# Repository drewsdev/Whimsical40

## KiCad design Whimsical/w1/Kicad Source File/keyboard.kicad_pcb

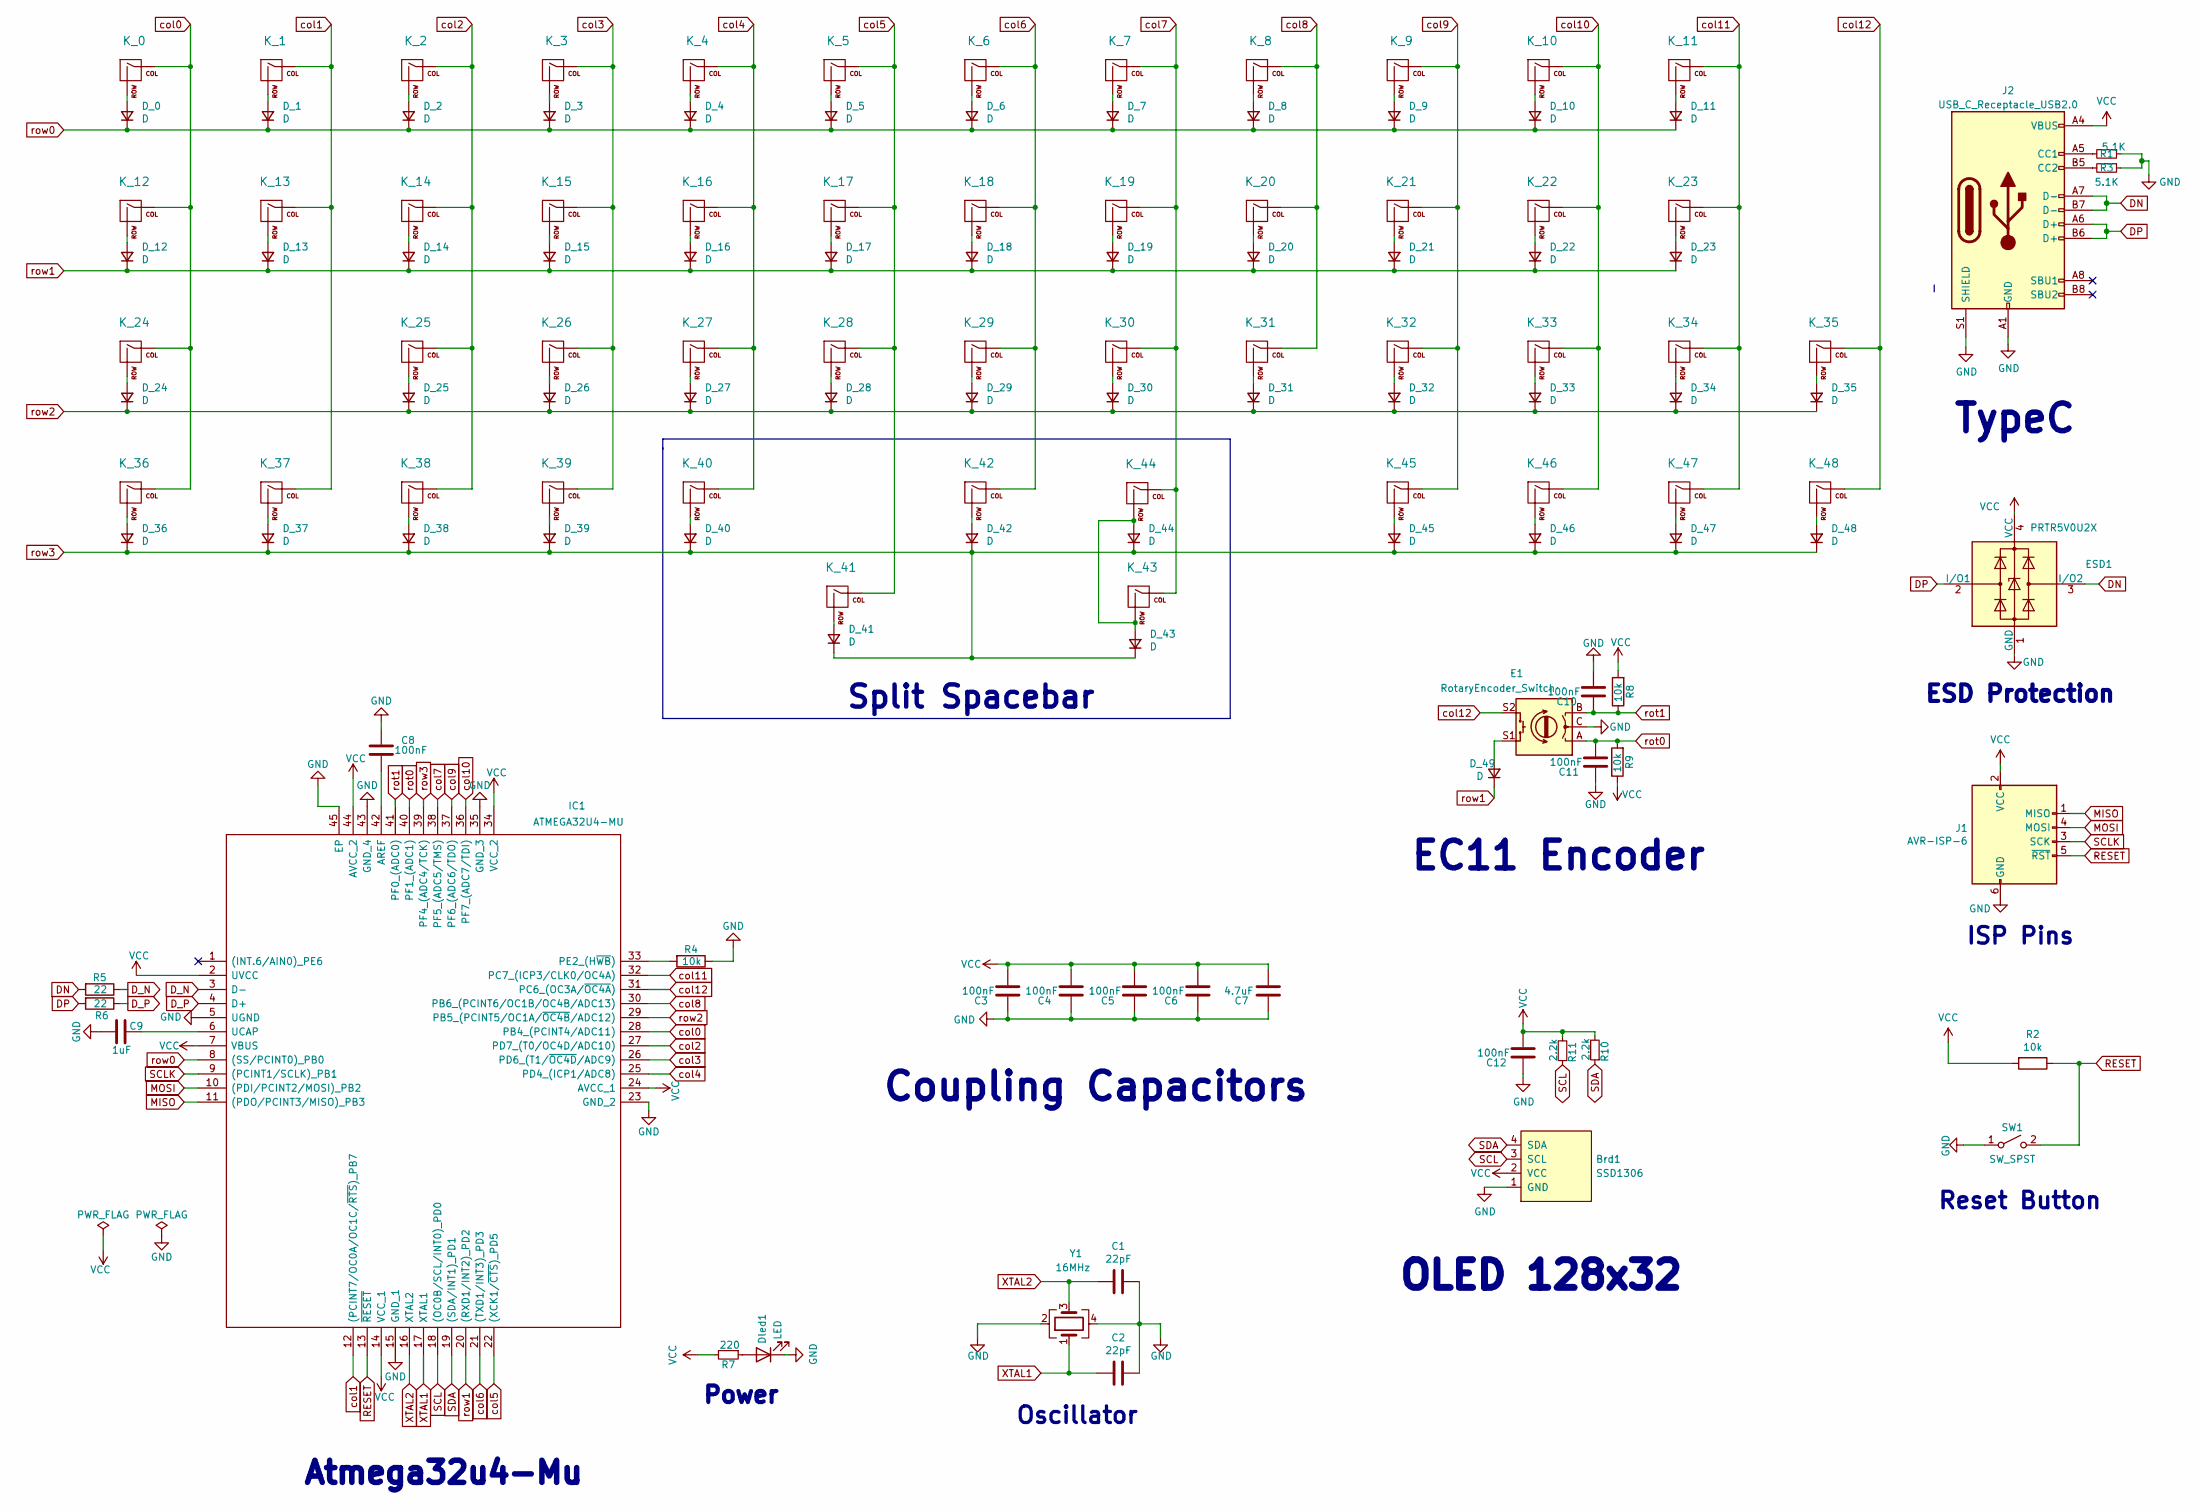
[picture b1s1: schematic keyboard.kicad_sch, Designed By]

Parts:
Brd1: SSD1306; 128x64OLED_128x64
C1, C2: 22pF; C_0603_1608Metric
C3, C4, C5, C6, C8, C10, C11, C12: 100nF; C_0603_1608Metric
C7: 4.7uF; C_0603_1608Metric
C9: 1uF; C_0603_1608Metric
D_0, D_1, D_2, D_3, D_4, D_5, D_6, D_7, D_8, D_9, D_10, D_11, D_12, D_13, D_14, D_15, D_16, D_17, D_18, D_19, D_20, D_21, D_22, D_23, D_24, D_25, D_26, D_27, D_28, D_29, D_30, D_31, D_32, D_33, D_34, D_35, D_36, D_37, D_38, D_39, D_40, D_41, D_42, D_43, D_44, D_45, D_46, D_47, D_48, D_49: D; D_SOD-123
Dled1: LED; LED_0603_1608Metric; LCSC C473820
E1: RotaryEncoder_Switch; RotaryEncoder_Alps_EC11E-Switch_Vertical_H20mm
ESD1: PRTR5V0U2X; LCSC C2827688
IC1: ATMEGA32U4-MU; QFN50P700X700X100-45N-D; Manufacturer_Part_Number ATMEGA32U4-MU; Mouser Part Number 556-ATMEGA32U4-MU
J1: AVR-ISP-6; ISP
J2: USB_C_Receptacle_USB2.0; USB_C_Receptacle_HRO_TYPE-C-31-M-12
K_0, K_1, K_2, K_3, K_4, K_5, K_6, K_7, K_8, K_9, K_10, K_13, K_14, K_15, K_16, K_17, K_18, K_19, K_20, K_21, K_22, K_25, K_26, K_27, K_28, K_29, K_30, K_31, K_32, K_33, K_34, K_35, K_36, K_37, K_38, K_39, K_45, K_46, K_47, K_48: KEYSW; MXOnly-1U-Hotswap-Solder
K_11, K_24: KEYSW; MX-1.5U-NoLED-solder
K_12, K_23, K_40, K_44: KEYSW; CherryMX_1.250u_PCB_KailhSocket-solder
K_41, K_43: KEYSW; MX-2.25U-ReversedStabilizers-NoLED-flip
K_42: KEYSW; Reverse-MXOnly-2U-Hotswap+normal
R1, R3: 5.1K; R_0603_1608Metric
R2: 10k; R_0603_1608Metric; LCSC Part # C17414
R4, R8, R9: 10k; R_0603_1608Metric
R5, R6: 22; R_0603_1608Metric
R7: 220; R_0603_1608Metric
R10, R11: 2.2k; R_0603_1608Metric
SW1: SW_SPST; K2-1187SQ-A4SW-06; Manufacturer Part Number K2-1187SQ-A4SW-06
Y1: 16MHz; Crystal_SMD_3225-4Pin_3.2x2.5mm; LCSC Part # C13738

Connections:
DN: ESD1.3 (I/O2), J2.A7 (D-), J2.B7 (D-), R5.2
DP: ESD1.2 (I/O1), J2.A6 (D+), J2.B6 (D+), R6.2
D_N: IC1.3 (D-), R5.1
D_P: IC1.4 (D+), R6.1
GND: Brd1.1 (GND), C1.1, C2.1, C3.2, C4.2, C5.2, C6.2, C7.2, C8.2, C9.2, C10.1, C11.2, C12.2, Dled1.1 (K), E1.C, ESD1.1 (GND), IC1.5 (UGND), IC1.15 (GND_1), IC1.23 (GND_2), IC1.35 (GND_3), IC1.43 (GND_4), IC1.45 (EP), J1.6 (GND), J2.A1 (GND), J2.A12 (GND), J2.B1 (GND), J2.B12 (GND), J2.S1 (SHIELD), R1.1, R3.1, R4.1, SW1.1 (A), Y1.2, Y1.4
MISO: IC1.11 ((PDO/PCINT3/MISO)_PB3), J1.1 (MISO)
MOSI: IC1.10 ((PDI/PCINT2/MOSI)_PB2), J1.4 (MOSI)
unnamed: C8.1, IC1.42 (AREF)
unnamed: C9.1, IC1.6 (UCAP)
unnamed: D_0.2 (A), K_0.2 (ROW)
unnamed: D_1.2 (A), K_1.2 (ROW)
unnamed: D_2.2 (A), K_2.2 (ROW)
unnamed: D_3.2 (A), K_3.2 (ROW)
unnamed: D_4.2 (A), K_4.2 (ROW)
unnamed: D_5.2 (A), K_5.2 (ROW)
unnamed: D_6.2 (A), K_6.2 (ROW)
unnamed: D_7.2 (A), K_7.2 (ROW)
unnamed: D_8.2 (A), K_8.2 (ROW)
unnamed: D_9.2 (A), K_9.2 (ROW)
unnamed: D_10.2 (A), K_10.2 (ROW)
unnamed: D_11.2 (A), K_11.2 (ROW)
unnamed: D_12.2 (A), K_12.2 (ROW)
unnamed: D_13.2 (A), K_13.2 (ROW)
unnamed: D_14.2 (A), K_14.2 (ROW)
unnamed: D_15.2 (A), K_15.2 (ROW)
unnamed: D_16.2 (A), K_16.2 (ROW)
unnamed: D_17.2 (A), K_17.2 (ROW)
unnamed: D_18.2 (A), K_18.2 (ROW)
unnamed: D_19.2 (A), K_19.2 (ROW)
unnamed: D_20.2 (A), K_20.2 (ROW)
unnamed: D_21.2 (A), K_21.2 (ROW)
unnamed: D_22.2 (A), K_22.2 (ROW)
unnamed: D_23.2 (A), K_23.2 (ROW)
unnamed: D_24.2 (A), K_24.2 (ROW)
unnamed: D_25.2 (A), K_25.2 (ROW)
unnamed: D_26.2 (A), K_26.2 (ROW)
unnamed: D_27.2 (A), K_27.2 (ROW)
unnamed: D_28.2 (A), K_28.2 (ROW)
unnamed: D_29.2 (A), K_29.2 (ROW)
unnamed: D_30.2 (A), K_30.2 (ROW)
unnamed: D_31.2 (A), K_31.2 (ROW)
unnamed: D_32.2 (A), K_32.2 (ROW)
unnamed: D_33.2 (A), K_33.2 (ROW)
unnamed: D_34.2 (A), K_34.2 (ROW)
unnamed: D_35.2 (A), K_35.2 (ROW)
unnamed: D_36.2 (A), K_36.2 (ROW)
unnamed: D_37.2 (A), K_37.2 (ROW)
unnamed: D_38.2 (A), K_38.2 (ROW)
unnamed: D_39.2 (A), K_39.2 (ROW)
unnamed: D_40.2 (A), K_40.2 (ROW)
unnamed: D_41.2 (A), K_41.2 (ROW)
unnamed: D_42.2 (A), K_42.2 (ROW)
unnamed: D_43.2 (A), D_44.2 (A), K_43.2 (ROW), K_44.2 (ROW)
unnamed: D_45.2 (A), K_45.2 (ROW)
unnamed: D_46.2 (A), K_46.2 (ROW)
unnamed: D_47.2 (A), K_47.2 (ROW)
unnamed: D_48.2 (A), K_48.2 (ROW)
unnamed: Dled1.2 (A), R7.1
unnamed: D_49.2 (A), E1.S1
unnamed: IC1.33 (PE2_(H~WB)), R4.2
unnamed: J2.A5 (CC1), R1.2
unnamed: J2.B5 (CC2), R3.2
RESET: IC1.13 (~RESET), J1.5 (~RST), R2.1, SW1.2 (B)
SCL: Brd1.3 (SCL), IC1.18 ((OC0B/SCL/INT0)_PD0), R11.1
SCLK: IC1.9 ((PCINT1/SCLK)_PB1), J1.3 (SCK)
SDA: Brd1.4 (SDA), IC1.19 ((SDA/INT1)_PD1), R10.1
VCC: Brd1.2 (VCC), C3.1, C4.1, C5.1, C6.1, C7.1, C12.1, ESD1.4 (VCC), IC1.2 (UVCC), IC1.7 (VBUS), IC1.14 (VCC_1), IC1.24 (AVCC_1), IC1.34 (VCC_2), IC1.44 (AVCC_2), J1.2 (VCC), J2.A4 (VBUS), J2.A9 (VBUS), J2.B4 (VBUS), J2.B9 (VBUS), R2.2, R7.2, R8.2, R9.1, R10.2, R11.2
XTAL1: C2.2, IC1.17 (XTAL1), Y1.1
XTAL2: C1.2, IC1.16 (XTAL2), Y1.3
col0: IC1.28 (PB4_(PCINT4/ADC11)), K_0.1 (COL), K_12.1 (COL), K_24.1 (COL), K_36.1 (COL)
col1: IC1.12 ((PCINT7/OC0A/OC1C/~RTS)_PB7), K_1.1 (COL), K_13.1 (COL), K_37.1 (COL)
col2: IC1.27 (PD7_(T0/OC4D/ADC10)), K_2.1 (COL), K_14.1 (COL), K_25.1 (COL), K_38.1 (COL)
col3: IC1.26 (PD6_(T1/~OC4D/ADC9)), K_3.1 (COL), K_15.1 (COL), K_26.1 (COL), K_39.1 (COL)
col4: IC1.25 (PD4_(ICP1/ADC8)), K_4.1 (COL), K_16.1 (COL), K_27.1 (COL), K_40.1 (COL)
col5: IC1.22 ((XCK1/~CTS)_PD5), K_5.1 (COL), K_17.1 (COL), K_28.1 (COL), K_41.1 (COL)
col6: IC1.21 ((TXD1/INT3)_PD3), K_6.1 (COL), K_18.1 (COL), K_29.1 (COL), K_42.1 (COL)
col7: IC1.38 (PF5_(ADC5/TMS)), K_7.1 (COL), K_19.1 (COL), K_30.1 (COL), K_43.1 (COL), K_44.1 (COL)
col8: IC1.30 (PB6_(PCINT6/OC1B/OC4B/ADC13)), K_8.1 (COL), K_20.1 (COL), K_31.1 (COL)
col9: IC1.37 (PF6_(ADC6/TDO)), K_9.1 (COL), K_21.1 (COL), K_32.1 (COL), K_45.1 (COL)
col10: IC1.36 (PF7_(ADC7/TDI)), K_10.1 (COL), K_22.1 (COL), K_33.1 (COL), K_46.1 (COL)
col11: IC1.32 (PC7_(ICP3/CLK0/OC4A)), K_11.1 (COL), K_23.1 (COL), K_34.1 (COL), K_47.1 (COL)
col12: E1.S2, IC1.31 (PC6_(OC3A/~OC4A)), K_35.1 (COL), K_48.1 (COL)
rot0: C11.1, E1.A, IC1.40 (PF1_(ADC1)), R9.2
rot1: C10.2, E1.B, IC1.41 (PF0_(ADC0)), R8.1
row0: D_0.1 (K), D_1.1 (K), D_2.1 (K), D_3.1 (K), D_4.1 (K), D_5.1 (K), D_6.1 (K), D_7.1 (K), D_8.1 (K), D_9.1 (K), D_10.1 (K), D_11.1 (K), IC1.8 ((SS/PCINT0)_PB0)
row1: D_12.1 (K), D_13.1 (K), D_14.1 (K), D_15.1 (K), D_16.1 (K), D_17.1 (K), D_18.1 (K), D_19.1 (K), D_20.1 (K), D_21.1 (K), D_22.1 (K), D_23.1 (K), D_49.1 (K), IC1.20 ((RXD1/INT2)_PD2)
row2: D_24.1 (K), D_25.1 (K), D_26.1 (K), D_27.1 (K), D_28.1 (K), D_29.1 (K), D_30.1 (K), D_31.1 (K), D_32.1 (K), D_33.1 (K), D_34.1 (K), D_35.1 (K), IC1.29 (PB5_(PCINT5/OC1A/~OC4B/ADC12))
row3: D_36.1 (K), D_37.1 (K), D_38.1 (K), D_39.1 (K), D_40.1 (K), D_41.1 (K), D_42.1 (K), D_43.1 (K), D_44.1 (K), D_45.1 (K), D_46.1 (K), D_47.1 (K), D_48.1 (K), IC1.39 (PF4_(ADC4/TCK))

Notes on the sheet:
Coupling Capacitors
Atmega32u4-Mu
ISP Pins
Reset Button
Power
ESD Protection
OLED 128x32
Oscillator
EC11 Encoder
TypeC
Split Spacebar

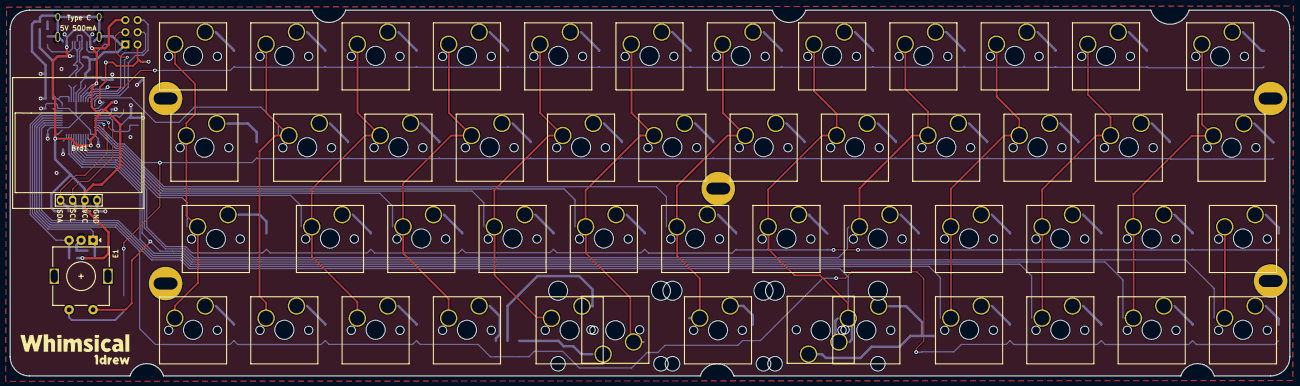
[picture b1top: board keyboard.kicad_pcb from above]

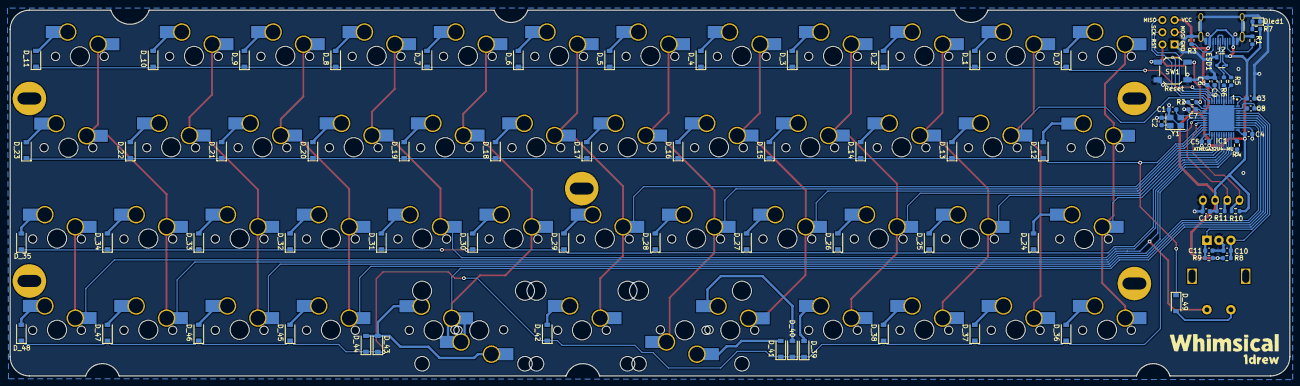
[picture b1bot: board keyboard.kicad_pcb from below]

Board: 2 copper layers, 267.0 x 76.3 mm, 131 parts (129 on the bottom side), 88 nets.

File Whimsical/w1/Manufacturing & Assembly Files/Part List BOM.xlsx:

Item | Qty | Reference(s) | Value | LibPart | Footprint | JLCPCB Part#
1 | 1 | Brd1 | SSD1306 | SSD1306-128x64_OLED:SSD1306 | SSD1306 OLED:128x64OLED_128x64 | https://www.aliexpress.com/i/32780054633.html
2 | 2 | C1, C2 | 22pF | Device:C | CherryMX_KailhSocket:C_0603_1608Metric | C1653
3 | 8 | C3, C4, C5, C6, C8, C10, C11, C12 | 100nF | Device:C | CherryMX_KailhSocket:C_0603_1608Metric | C14663
4 | 1 | C7 | 4.7uF | Device:C | CherryMX_KailhSocket:C_0603_1608Metric | C19666
5 | 1 | C9 | 1uF | Device:C | CherryMX_KailhSocket:C_0603_1608Metric | C15849
6 | 50 | D_0, D_1, D_2, D_3, D_4, D_5, D_6, D_7, D_8, D_9, D_10, D_11, D_12, D_13, D_14,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 | D | Device:D_Small | Diode_SMD:D_SOD-123 | C81598
7 | 1 | Dled1 | LED | Device:LED | LED_SMD:LED_0603_1608Metric | C72038
8 | 1 | E1 | RotaryEncoder_Switch | Device:RotaryEncoder_Switch | CherryMX_KailhSocket:RotaryEncoder_Alps_EC11E-Switch_Vertical_H20mm | C1322545
9 | 1 | ESD1 | PRTR5V0U2X | Power_Protection:PRTR5V0U2X | CherryMX_KailhSocket:PRTR5V0U2X | C2827688
10 | 1 | IC1 | ATMEGA32U4-MU | ATMEGA32U4-MU:ATMEGA32U4-MU | QFN50P700X700X100-45N-D | C112161
11 | 1 | J2 | USB_C_Receptacle_USB2.0 | :USB_C_Receptacle_USB2.0_1 | CherryMX_KailhSocket:USB_C_Receptacle_HRO_TYPE-C-31-M-12 | C165948
12 | 40 | K_0, K_1, K_2, K_3, K_4, K_5, K_6, K_7, K_8, K_9, K_10, K_13, K_14, K_15, K_16,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 | KEYSW | MX_Alps_Hybrid:MX-NoLED | CherryMX_KailhSocket:MXOnly-1U-Hotswap-Solder | C2803348
13 | 2 | K_11, K_24 | KEYSW | MX_Alps_Hybrid:MX-NoLED | CherryMX_KailhSocket:MX-1.5U-NoLED-solder | C2803348
14 | 4 | K_12, K_23, K_40, K_44 | KEYSW | MX_Alps_Hybrid:MX-NoLED | CherryMX_KailhSocket:CherryMX_1.250u_PCB_KailhSocket-solder | C2803348
15 | 2 | K_41, K_43 | KEYSW | MX_Alps_Hybrid:MX-NoLED | CherryMX_KailhSocket:MX-2.25U-ReversedStabilizers-NoLED-flip | C2803348
16 | 1 | K_42 | KEYSW | MX_Alps_Hybrid:MX-NoLED | CherryMX_KailhSocket:Reverse-MXOnly-2U-Hotswap+normal | C2803348
17 | 2 | R1, R3 | 5.1K | Device:R_Small | Resistor_SMD:R_0603_1608Metric | C23186
18 | 4 | R2, R4, R8, R9 | 10k | Device:R | CherryMX_KailhSocket:R_0603_1608Metric | C25804
19 | 2 | R5, R6 | 22 | Device:R | CherryMX_KailhSocket:R_0603_1608Metric | C23345
20 | 1 | R7 | 220 | Device:R_Small | CherryMX_KailhSocket:R_0603_1608Metric | C22962
21 | 2 | R10, R11 | 2.2k | Device:R_Small | CherryMX_KailhSocket:R_0603_1608Metric | C4190
22 | 1 | SW1 | SW_SPST | Switch:SW_SPST | CherryMX_KailhSocket:K2-1187SQ-A4SW-06 | C92584
23 | 1 | Y1 | 16MHz | Device:Crystal_GND24 | CherryMX_KailhSocket:Crystal_SMD_3225-4Pin_3.2x2.5mm | C13738

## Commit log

2026-04-22 Upload Whimsical Files
